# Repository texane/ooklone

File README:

For more info, please read the article here:
http://www.embeddedrelated.com/showarticle/626.php
Also, this project was submitted to the Hackaday Prize Contest:
http://hackaday.io/project/2403-ooklone

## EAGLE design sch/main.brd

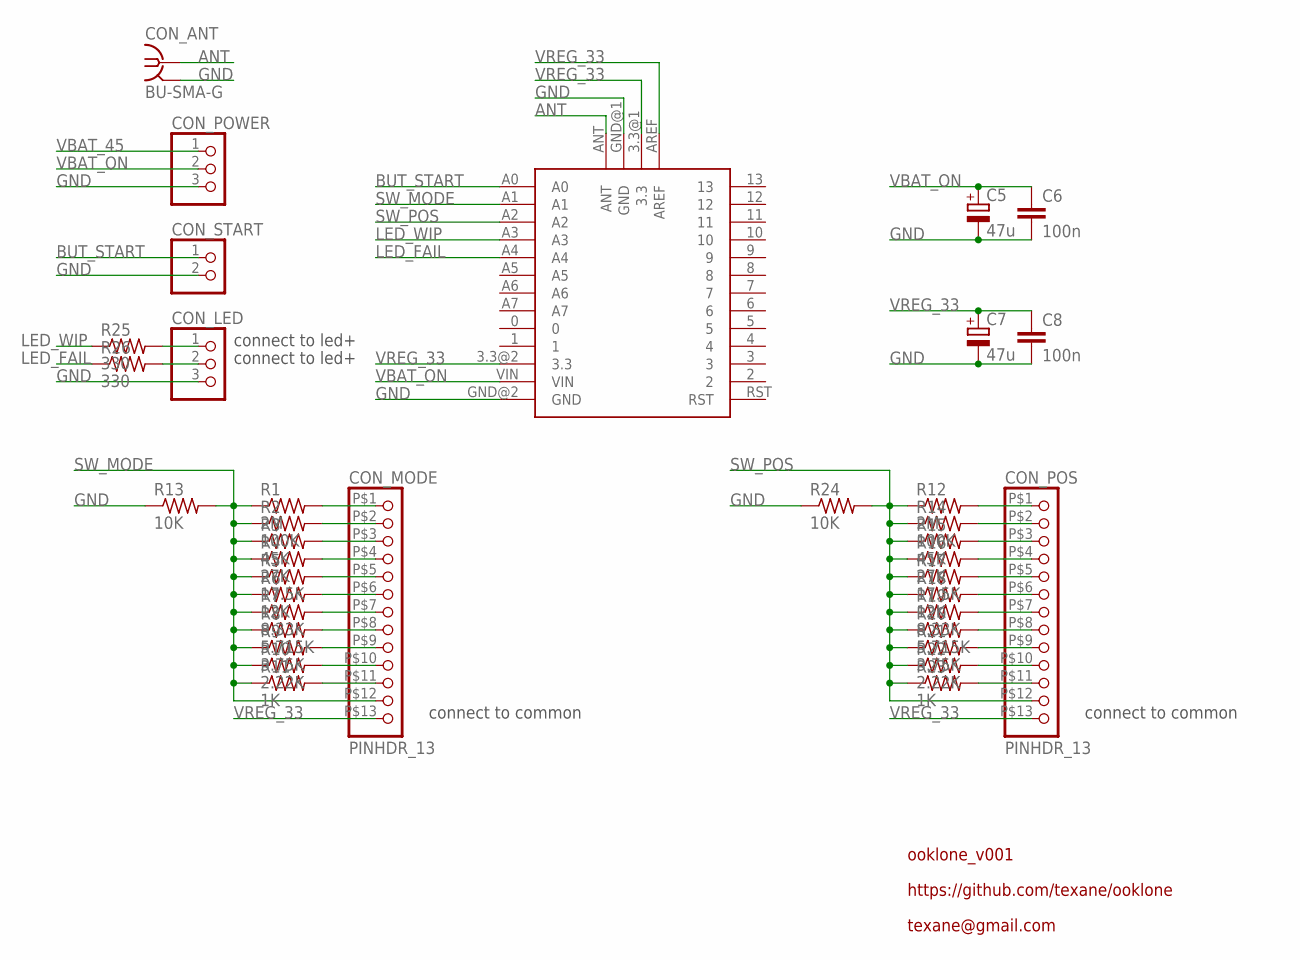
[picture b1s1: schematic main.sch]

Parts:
C5, C7: 47u; PANASONIC_D
C6, C8: 100n; C1206K
CON_ANT: BU-SMA-G
CON_LED: PINHD-1X3; 1X03
CON_MODE: PINHDR_13
CON_POS: PINHDR_13
CON_POWER: PINHD-1X3; 1X03
CON_START: PINHD-1X2; 1X02
R1, R12: 2M; R1206
R2, R14: 100K; R1206
R3, R15: 45K; R1206
R4, R16: 27K; R1206
R5, R17: 17.5K; R1206
R6, R18: 12K; R1206
R7, R19: 8.33K; R1206
R8, R20: 5.715K; R1206
R9, R21: 3.75K; R1206
R10, R22: 2.22K; R1206
R11, R23: 1K; R1206
R13, R24: 10K; R1206
R25, R26: 330; R1206
U$1: MOTEINO_USB_R4

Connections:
ANT: CON_ANT.1, U$1.ANT
BUT_START: CON_START.1, U$1.A0
GND: C5.-, C6.2, C7.-, C8.2, CON_ANT.2, CON_ANT.3 (2), CON_ANT.4 (2), CON_ANT.5 (2), CON_LED.3, CON_POWER.3, CON_START.2, R13.1, R24.1, U$1.GND@1 (GND), U$1.GND@2 (GND)
LED_FAIL: R26.1, U$1.A4
LED_WIP: R25.1, U$1.A3
unnamed: CON_MODE.P$1 (1), R1.2
unnamed: CON_MODE.P$2 (2), R2.2
unnamed: CON_MODE.P$3 (3), R3.2
unnamed: CON_MODE.P$4 (4), R4.2
unnamed: CON_MODE.P$5 (5), R5.2
unnamed: CON_MODE.P$6 (6), R6.2
unnamed: CON_MODE.P$7 (7), R7.2
unnamed: CON_MODE.P$8 (8), R8.2
unnamed: CON_MODE.P$9 (9), R9.2
unnamed: CON_MODE.P$10 (10), R10.2
unnamed: CON_MODE.P$11 (11), R11.2
unnamed: CON_POS.P$1 (1), R12.2
unnamed: CON_POS.P$2 (2), R14.2
unnamed: CON_POS.P$3 (3), R15.2
unnamed: CON_POS.P$4 (4), R16.2
unnamed: CON_POS.P$5 (5), R17.2
unnamed: CON_POS.P$6 (6), R18.2
unnamed: CON_POS.P$7 (7), R19.2
unnamed: CON_POS.P$8 (8), R20.2
unnamed: CON_POS.P$9 (9), R21.2
unnamed: CON_POS.P$10 (10), R22.2
unnamed: CON_POS.P$11 (11), R23.2
unnamed: CON_LED.1, R25.2
unnamed: CON_LED.2, R26.2
SW_MODE: CON_MODE.P$12 (12), R1.1, R2.1, R3.1, R4.1, R5.1, R6.1, R7.1, R8.1, R9.1, R10.1, R11.1, R13.2, U$1.A1
SW_POS: CON_POS.P$12 (12), R12.1, R14.1, R15.1, R16.1, R17.1, R18.1, R19.1, R20.1, R21.1, R22.1, R23.1, R24.2, U$1.A2
VBAT_45: CON_POWER.1
VBAT_ON: C5.+, C6.1, CON_POWER.2, U$1.VIN
VREG_33: C7.+, C8.1, CON_MODE.P$13 (13), CON_POS.P$13 (13), U$1.3.3@1 (3.3), U$1.3.3@2 (3.3), U$1.AREF

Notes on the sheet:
connect to led+
connect to common
ooklone_v001
https://github.com/texane/ooklone
texane@gmail.com

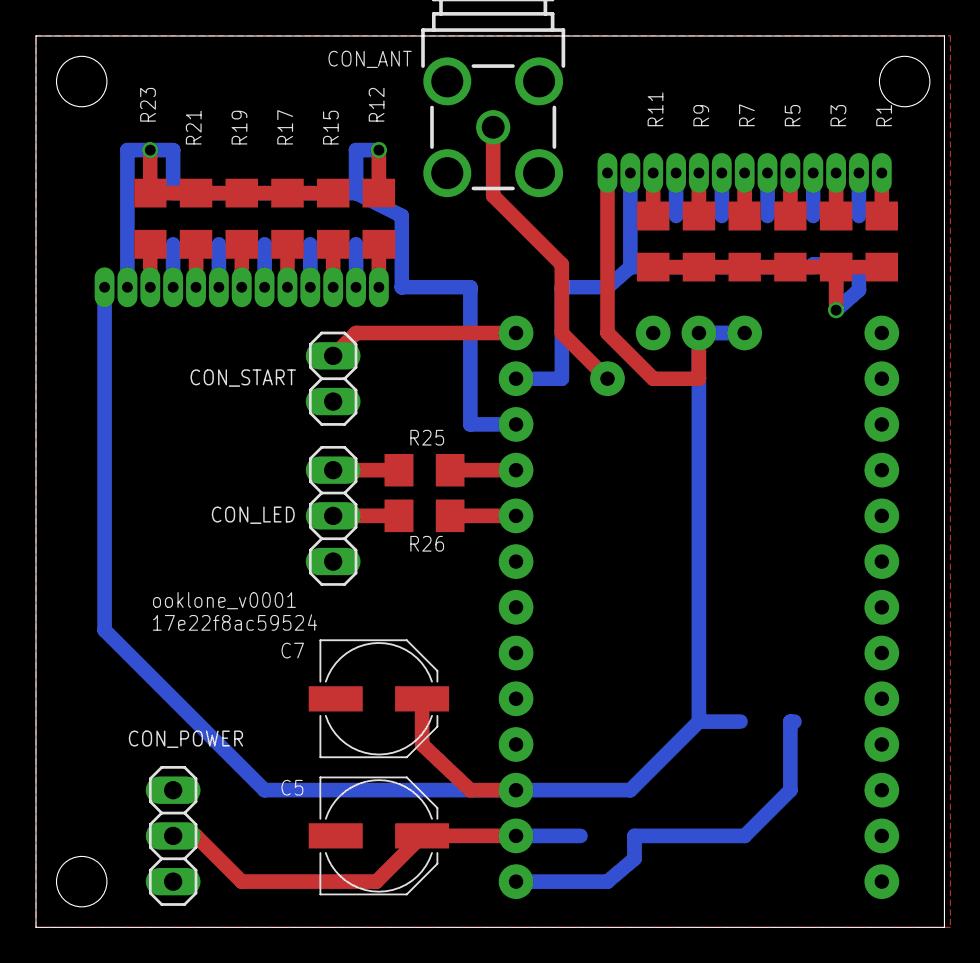
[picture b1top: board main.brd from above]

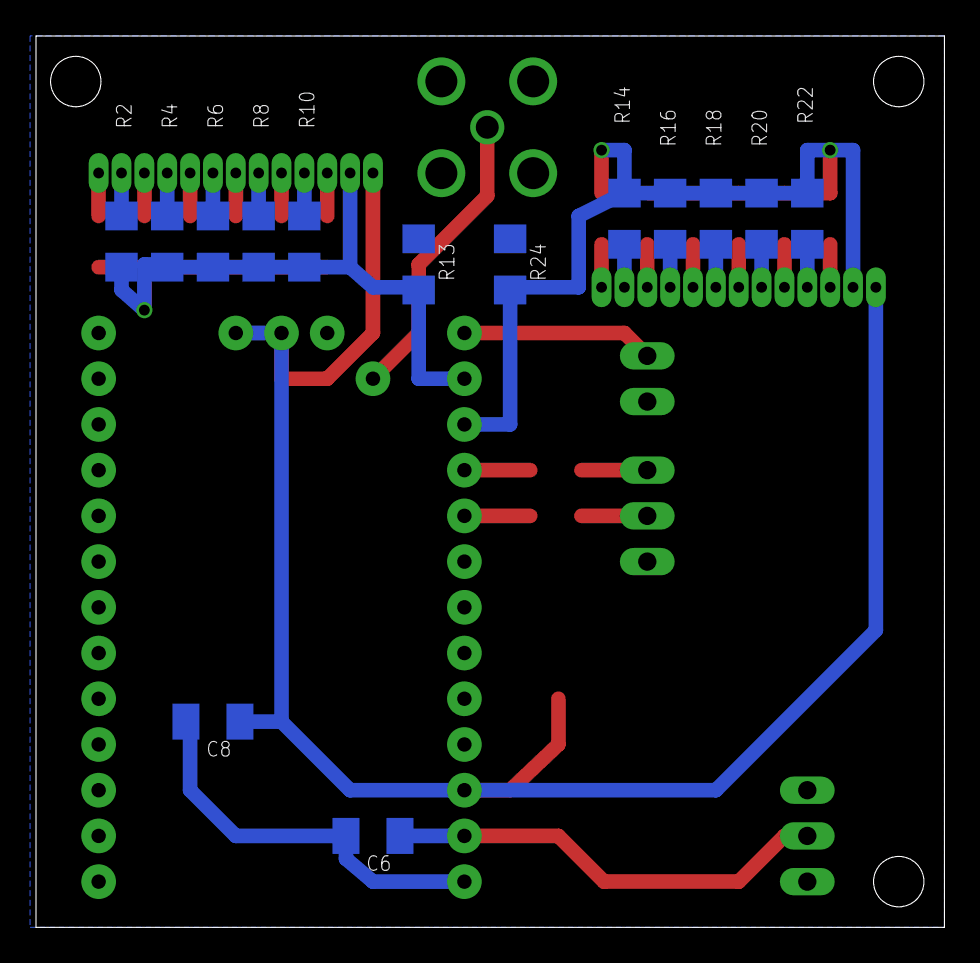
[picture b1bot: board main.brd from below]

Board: 2 copper layers, 50.5 x 49.5 mm, 37 parts (14 on the bottom side), 33 nets.

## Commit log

2014-08-05 [ add ] doc, src
2014-08-06 [ update ] continuous ook mode with fixed rssi threshold
2014-08-06 [ update ] pulse slicer
2014-08-06 [ update ] tx continuous mode
2014-08-07 [ update ] remove dio4, add dio1 for dclk
2014-08-07 [ update ] fill with castoplug signal
2014-08-07 [ update ] ook peak versus fixed
2014-08-08 [ update ] frf write comment
2014-08-08 [ update ] pcint mode, pulse filtering
2014-08-09 [ update ] works with castoplug
2014-08-09 [ update ] add PULSE_TIMER_RES_US
2014-08-09 [ add ] pic/scaled
2014-08-10 [ update ] CONFIG_UART
2014-08-12 [ add ] pics
2014-08-12 [ update ] rfm69_write_pa_level
2014-08-12 [ update ] button support
2014-08-12 [ update ] sleep while waiting for button
2014-08-12 [ update ] no but_pcint_pins reset to handle continuous press
2014-08-12 [ update ] code cleanup
2014-08-13 [ add ] doc/vid/readme
2014-08-13 [ add ] README
2014-08-15 [ update ] rotary_switch resistor computation tool
2014-08-15 [ update ] rotary_switch resistor computation tool missing table
2014-08-15 [ update ] rotary_switch tool, change to 7 positions
2014-08-16 [ update ] rotary_switch tool, add actual resistor values
2014-08-16 [ update ] 7 position rotary switch added
2014-08-16 [ update ] comments
2014-08-16 [ update ] pic/scaled
2014-08-16 [ update ] clean rotary switch code
2014-08-16 [ update ] rotary switch notes
2014-08-16 [ update ] sel_test
2014-08-16 [ update ] per frame slicer context
2014-08-17 [ update ] PULSE_MAX_TIMER fixed to 0xff, pulse_all_eofs
2014-08-17 [ update ] exact 433.92MHz carrier frequency computation
2014-08-17 [ add ] clio locking demo patch. wont be required when flash support implemented
2014-08-17 [ add, update ] src/flash.c. move spi_setup_master in main. add spi_xxx_512 routines.
2014-08-17 [ update, fix ] flash invalid subsector address computation, better unit test
2014-08-18 [ update ] use flash to store and load frames
2014-08-18 [ update ] rfm69_get_rssi_avg
2014-08-18 [ update ] UART_WRITE_STRING
2014-08-18 [ add ] doc/todo
2014-08-18 [ update ] doc/todo
2014-08-18 [ add ] src/avcc.c
2014-08-18 [ update ] todo
2014-08-19 [ add ] logo/0001
2014-08-19 [ add ] logo/0002
2014-08-20 [ add ] logo/0003
2014-08-20 [ update ] doc/system_design missing ground
2014-08-20 [ add ] doc/system_design
2014-08-20 [ add ] doc/user_interface
2014-08-20 [ update ] README
2014-08-27 [ update ] sch/moteino_usb_r4.lbr
2014-08-27 [ add ] moteino_usb_r4.lbr
2014-08-28 [ add ] sch/STM-LF33ABDT-TR library
2014-08-28 [ add ] sch/main.bom
2014-08-28 [ add ] sch/main.sch
2014-08-28 [ update ] schematics, rotary switch util
2014-08-30 [ update ] schematics, bom
2014-09-13 [ add ] main.brd pinhdr_13.lbr
2014-09-13 [ update ] schematics, routing
2014-09-14 [ update ] todo, sma footprint ok
2014-09-14 [ update ] silkscreen cleaned
2014-09-14 [ update ] schematics frame
2014-09-14 [ update ] add name and version on silkscreen
2014-09-14 [ update ] add name git commit on silkscreen
2014-09-14 [ add ] sch/main.pdf
2014-09-14 [ rm ] sch/main.todo
2014-09-15 [ add ] solidworks
2014-09-18 [ add ] sr2611 1 pole 12 positions rotary switch
2014-09-18 [ add ] battery holder, grayhill rotary switch
2014-09-18 [ rm ] tildes
2014-09-18 [ update ] bom, on off switch and start button
2014-09-19 [ add ] MFS106D switch
2014-09-19 [ add ] R13-509B-05-BB.SLDPRT push button
2014-09-19 [ update ] minor
2014-09-19 [ add ] led
2014-09-19 [ add ] screw_m2.5
2014-09-21 [ add ] enclosure STL
2014-09-21 [ add ] all.PNG
2014-09-22 [ add ] front,back_inches.STL
2014-09-22 [ update ] main.bom
2014-10-11 [ fix ] gnd ant signal inversion
2014-10-11 [ update ] schematics version, silkscreen
2014-10-11 [ add ] pcb v0000 pictures
2014-10-16 [ add ] 3d printed enclosure pictures
2015-07-12 PULSE_TIMER_RES_US == 32
2015-07-13 update CONTRIBS
